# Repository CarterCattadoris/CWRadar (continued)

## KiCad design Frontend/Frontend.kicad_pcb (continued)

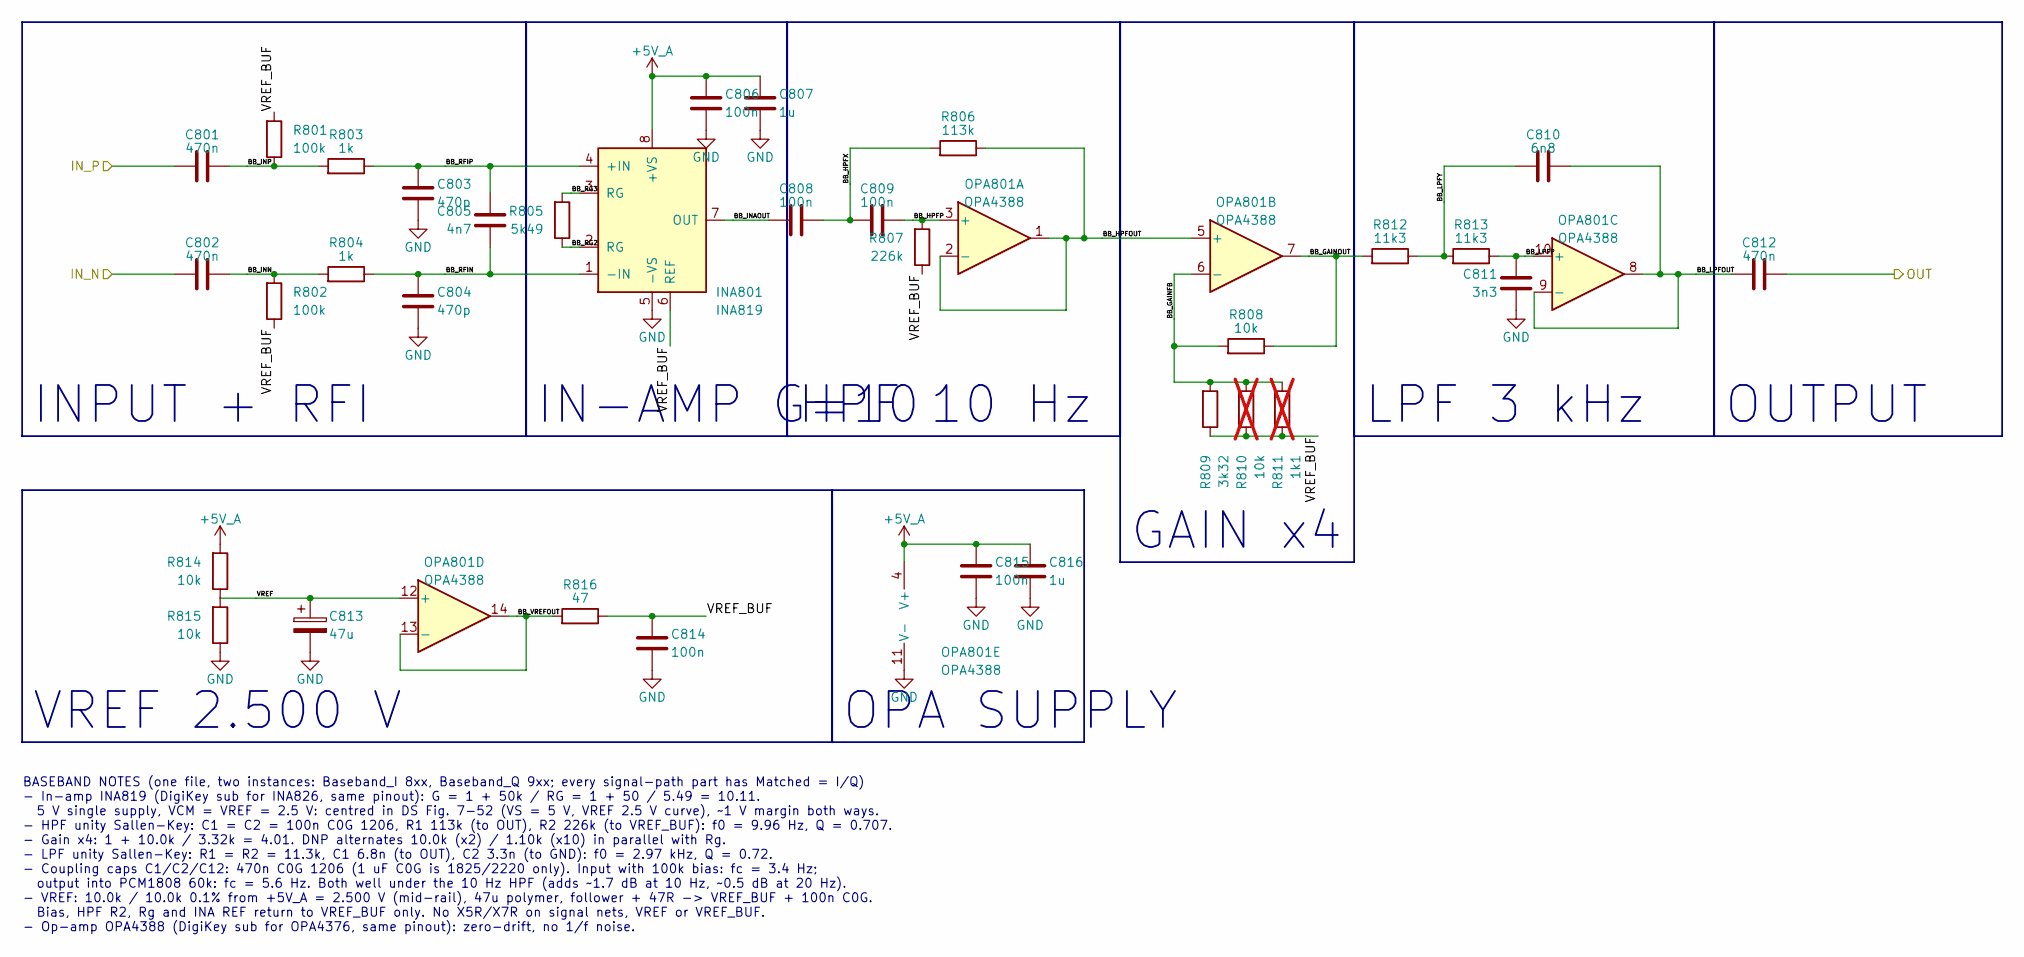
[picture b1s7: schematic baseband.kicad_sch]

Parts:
C801, C802, C812: 470n; C_1206_3216Metric; Mfg Part # GRM31C5C1E474JE01L
C803, C804: 470p; C_0402_1005Metric; Mfg Part # GRM1555C1H471GA01D
C805: 4n7; C_0603_1608Metric; Mfg Part # GCM1885C1H472GA16D
C806, C815: 100n; C_0402_1005Metric; Mfg Part # CL05B104KB54PNC; LCSC C307331
C807, C816: 1u; C_0603_1608Metric; Mfg Part # C0603C105K3RACTU
C808, C809, C814: 100n; C_1206_3216Metric; Mfg Part # GRM3195C2A104GA01D
C810: 6n8; C_0603_1608Metric; Mfg Part # C0603C682F5GACTU
C811: 3n3; C_0603_1608Metric; Mfg Part # GCM1885C1H332FA16D
C813: 47u; CP_EIA-3528-21_Kemet-B; Mfg Part # T520B476M010ATE070
INA801: INA819; SOIC-8_3.9x4.9mm_P1.27mm; Mfg Part # INA819IDR
OPA801: OPA4388; TSSOP-14_4.4x5mm_P0.65mm; Mfg Part # OPA4388IPWR
R801, R802: 100k; R_0402_1005Metric; Mfg Part # RC0402FR-07100KL
R803, R804: 1k; R_0402_1005Metric; Mfg Part # RC0402FR-071KL
R805: 5k49; R_0402_1005Metric; Mfg Part # ERA-2AEB5491X
R806: 113k; R_0402_1005Metric; Mfg Part # RC0402FR-07113KL
R807: 226k; R_0402_1005Metric; Mfg Part # ERJ-2RKF2263X
R808, R814, R815: 10k; R_0402_1005Metric; Mfg Part # ERA-2AEB103X
R809: 3k32; R_0402_1005Metric; Mfg Part # ERA-2AEB3321X
R810: 10k; R_0402_1005Metric; Mfg Part # ERA-2AEB103X; not fitted
R811: 1k1; R_0402_1005Metric; Mfg Part # RG1005P-112-B-T5; not fitted
R812, R813: 11k3; R_0402_1005Metric; Mfg Part # RC0402FR-0711K3L
R816: 47; R_0402_1005Metric; Mfg Part # RC0402FR-0747RL

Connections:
+5V_A: C806.1, C807.1, C815.1, C816.1, INA801.8 (+VS), OPA801.4 (V+), R814.1; also elsewhere on the board
/ADC/ADC_L: C812.2; also elsewhere on the board
/Baseband_I/BB_GAINFB: OPA801.6 (-), R808.1, R809.1, R810.1, R811.1
/Baseband_I/BB_GAINOUT: OPA801.7, R808.2, R812.1
/Baseband_I/BB_HPFOUT: OPA801.1, OPA801.2 (-), OPA801.5 (+), R806.2
/Baseband_I/BB_HPFP: C809.2, OPA801.3 (+), R807.1
/Baseband_I/BB_HPFX: C808.2, C809.1, R806.1
/Baseband_I/BB_INAOUT: C808.1, INA801.7 (OUT)
/Baseband_I/BB_INN: C802.2, R802.1, R804.1
/Baseband_I/BB_INP: C801.2, R801.2, R803.1
/Baseband_I/BB_LPFOUT: C810.2, C812.1, OPA801.8, OPA801.9 (-)
/Baseband_I/BB_LPFP: C811.1, OPA801.10 (+), R813.2
/Baseband_I/BB_LPFY: C810.1, R812.2, R813.1
/Baseband_I/BB_RFIN: C804.1, C805.2, INA801.1 (-IN), R804.2
/Baseband_I/BB_RFIP: C803.1, C805.1, INA801.4 (+IN), R803.2
/Baseband_I/BB_RG2: INA801.2 (RG), R805.2
/Baseband_I/BB_RG3: INA801.3 (RG), R805.1
/Baseband_I/BB_VREFOUT: OPA801.13 (-), OPA801.14, R816.1
/Baseband_I/IN_N: C802.1; also elsewhere on the board
/Baseband_I/IN_P: C801.1; also elsewhere on the board
/Baseband_I/VREF: C813.1, OPA801.12 (+), R814.2, R815.1
/Baseband_I/VREF_BUF: C814.1, INA801.6 (REF), R801.1, R802.2, R807.2, R809.2, R810.2, R811.2, R816.2
GND: C803.2, C804.2, C806.2, C807.2, C811.2, C813.2, C814.2, C815.2, C816.2, INA801.5 (-VS), OPA801.11 (V-), R815.2; also elsewhere on the board

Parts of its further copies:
C901, C902, C912: 470n; C_1206_3216Metric; Mfg Part # GRM31C5C1E474JE01L
C903, C904: 470p; C_0402_1005Metric; Mfg Part # GRM1555C1H471GA01D
C905: 4n7; C_0603_1608Metric; Mfg Part # GCM1885C1H472GA16D
C906, C915: 100n; C_0402_1005Metric; Mfg Part # CL05B104KB54PNC; LCSC C307331
C907, C916: 1u; C_0603_1608Metric; Mfg Part # C0603C105K3RACTU
C908, C909, C914: 100n; C_1206_3216Metric; Mfg Part # GRM3195C2A104GA01D
C910: 6n8; C_0603_1608Metric; Mfg Part # C0603C682F5GACTU
C911: 3n3; C_0603_1608Metric; Mfg Part # GCM1885C1H332FA16D
C913: 47u; CP_EIA-3528-21_Kemet-B; Mfg Part # T520B476M010ATE070
INA901: INA819; SOIC-8_3.9x4.9mm_P1.27mm; Mfg Part # INA819IDR
OPA901: OPA4388; TSSOP-14_4.4x5mm_P0.65mm; Mfg Part # OPA4388IPWR
R901, R902: 100k; R_0402_1005Metric; Mfg Part # RC0402FR-07100KL
R903, R904: 1k; R_0402_1005Metric; Mfg Part # RC0402FR-071KL
R905: 5k49; R_0402_1005Metric; Mfg Part # ERA-2AEB5491X
R906: 113k; R_0402_1005Metric; Mfg Part # RC0402FR-07113KL
R907: 226k; R_0402_1005Metric; Mfg Part # ERJ-2RKF2263X
R908, R914, R915: 10k; R_0402_1005Metric; Mfg Part # ERA-2AEB103X
R909: 3k32; R_0402_1005Metric; Mfg Part # ERA-2AEB3321X
R910: 10k; R_0402_1005Metric; Mfg Part # ERA-2AEB103X; not fitted
R911: 1k1; R_0402_1005Metric; Mfg Part # RG1005P-112-B-T5; not fitted
R912, R913: 11k3; R_0402_1005Metric; Mfg Part # RC0402FR-0711K3L
R916: 47; R_0402_1005Metric; Mfg Part # RC0402FR-0747RL

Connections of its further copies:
+5V_A: C906.1, C907.1, C915.1, C916.1, INA901.8 (+VS), OPA901.4 (V+), R914.1; also elsewhere on the board
/ADC/ADC_R: C912.2; also elsewhere on the board
/Baseband_Q/BB_GAINFB: OPA901.6 (-), R908.1, R909.1, R910.1, R911.1
/Baseband_Q/BB_GAINOUT: OPA901.7, R908.2, R912.1
/Baseband_Q/BB_HPFOUT: OPA901.1, OPA901.2 (-), OPA901.5 (+), R906.2
/Baseband_Q/BB_HPFP: C909.2, OPA901.3 (+), R907.1
/Baseband_Q/BB_HPFX: C908.2, C909.1, R906.1
/Baseband_Q/BB_INAOUT: C908.1, INA901.7 (OUT)
/Baseband_Q/BB_INN: C902.2, R902.1, R904.1
/Baseband_Q/BB_INP: C901.2, R901.2, R903.1
/Baseband_Q/BB_LPFOUT: C910.2, C912.1, OPA901.8, OPA901.9 (-)
/Baseband_Q/BB_LPFP: C911.1, OPA901.10 (+), R913.2
/Baseband_Q/BB_LPFY: C910.1, R912.2, R913.1
/Baseband_Q/BB_RFIN: C904.1, C905.2, INA901.1 (-IN), R904.2
/Baseband_Q/BB_RFIP: C903.1, C905.1, INA901.4 (+IN), R903.2
/Baseband_Q/BB_RG2: INA901.2 (RG), R905.2
/Baseband_Q/BB_RG3: INA901.3 (RG), R905.1
/Baseband_Q/BB_VREFOUT: OPA901.13 (-), OPA901.14, R916.1
/Baseband_Q/IN_N: C902.1; also elsewhere on the board
/Baseband_Q/IN_P: C901.1; also elsewhere on the board
/Baseband_Q/VREF: C913.1, OPA901.12 (+), R914.2, R915.1
/Baseband_Q/VREF_BUF: C914.1, INA901.6 (REF), R901.1, R902.2, R907.2, R909.2, R910.2, R911.2, R916.2
GND: C903.2, C904.2, C906.2, C907.2, C911.2, C913.2, C914.2, C915.2, C916.2, INA901.5 (-VS), OPA901.11 (V-), R915.2; also elsewhere on the board

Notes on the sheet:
INPUT + RFI
IN-AMP G=10
HPF 10 Hz
GAIN x4
LPF 3 kHz
OUTPUT
VREF 2.500 V
OPA SUPPLY
BASEBAND NOTES (one file, two instances: Baseband_I 8xx, Baseband_Q 9xx; every signal-path part has Matched = I/Q) - In-amp INA819 (DigiKey sub for INA826, same pinout): G = 1 + 50k / RG = 1 + 50 / 5.49 = 10.11. 5 V single supply, VCM = VREF = 2.5 V: centred in DS Fig. 7-52 (VS = 5 V, VREF 2.5 V cu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

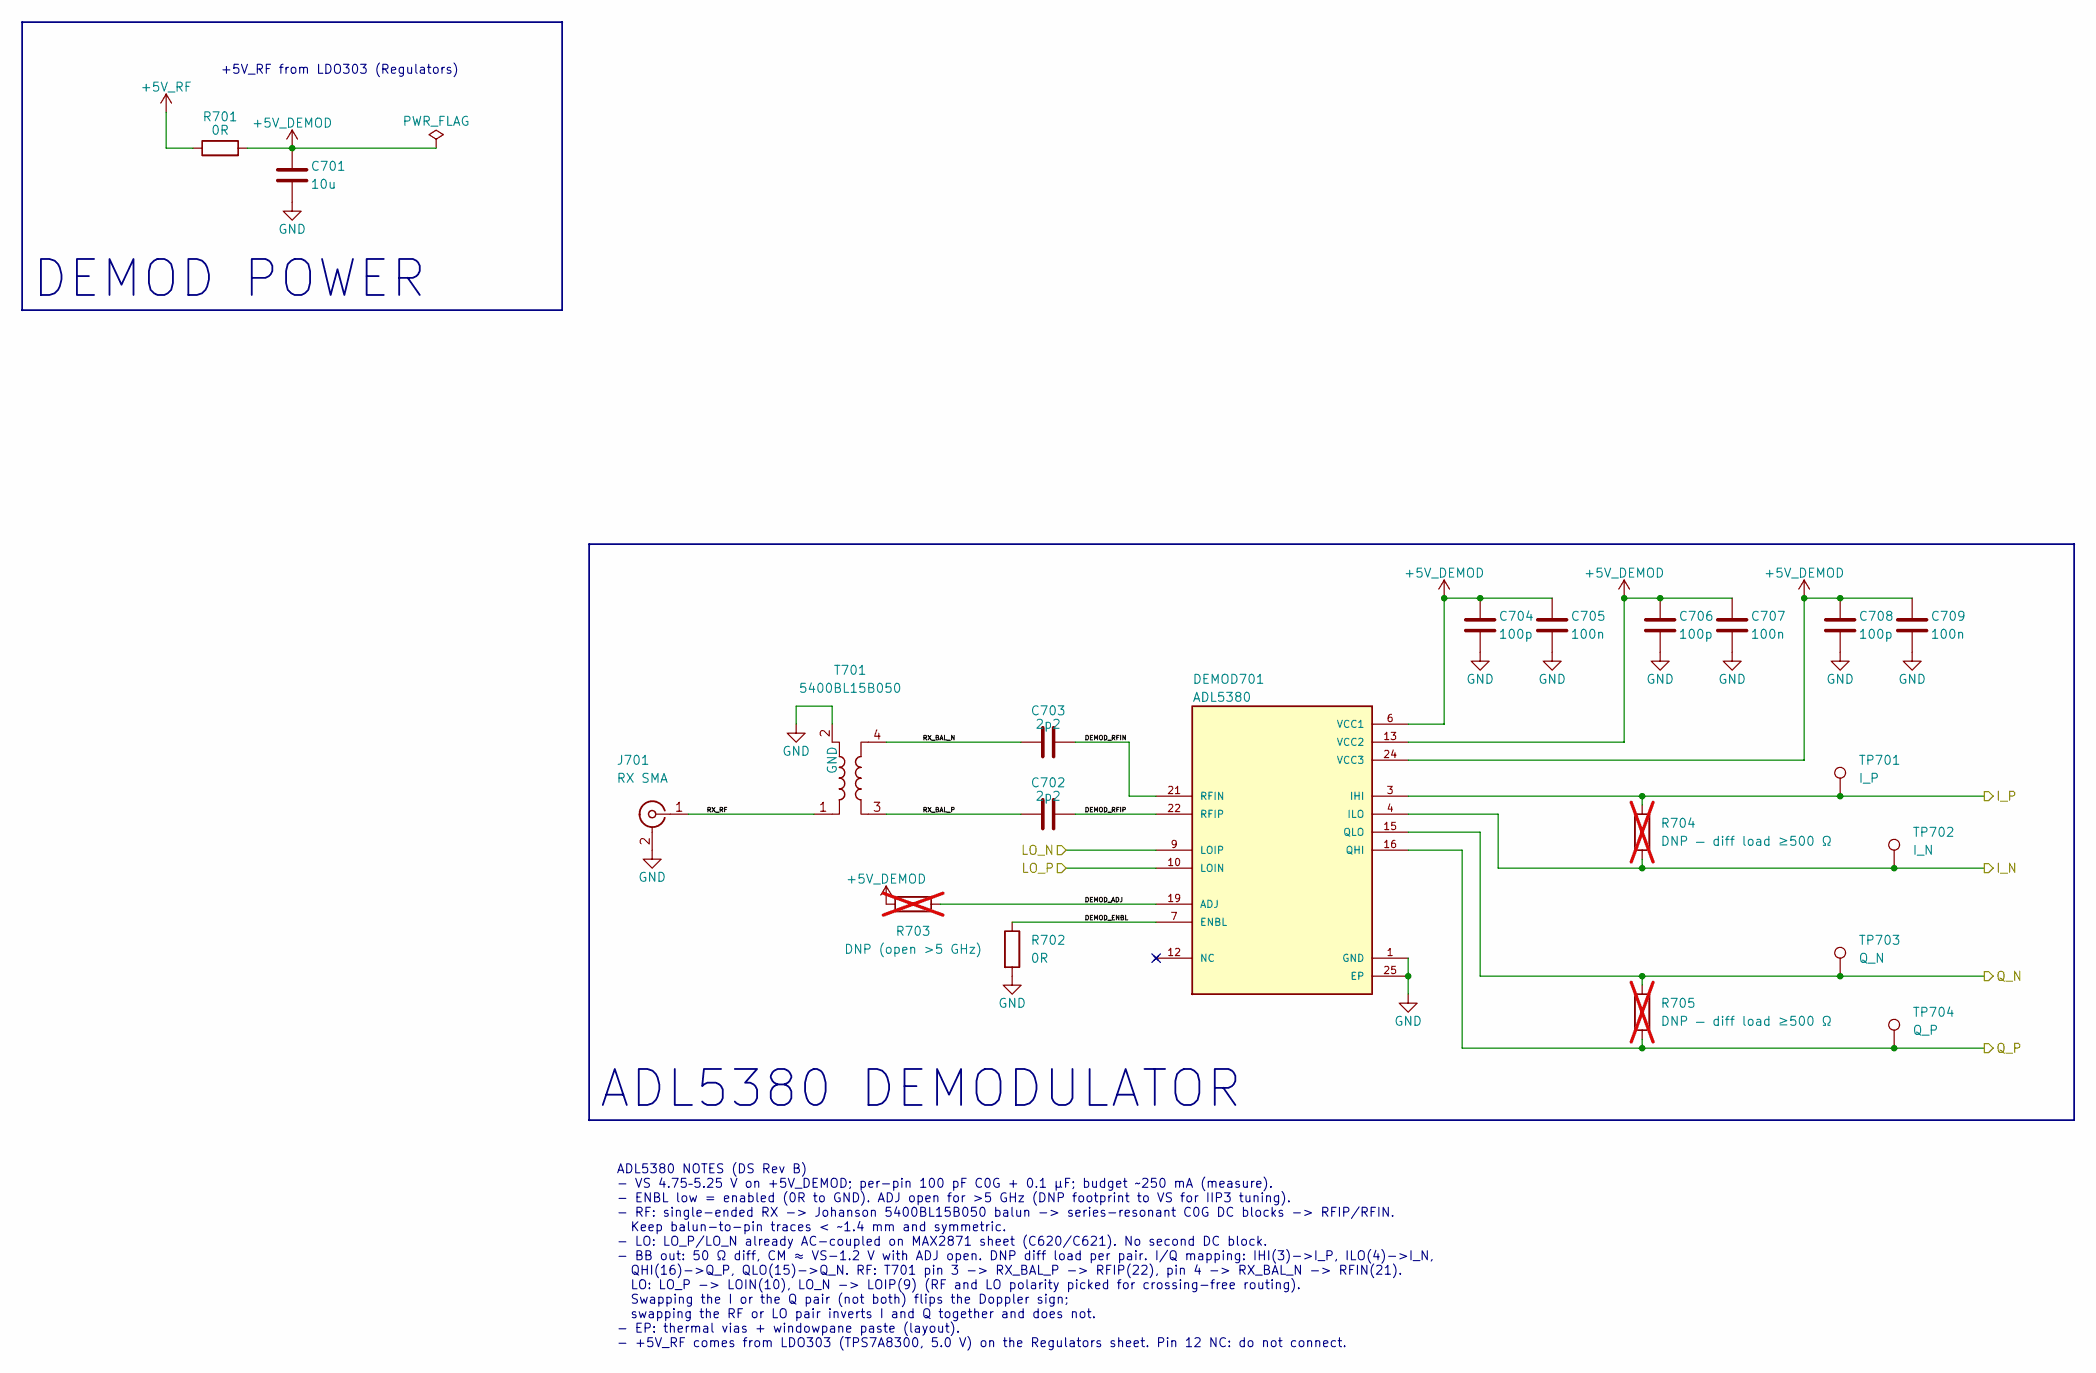
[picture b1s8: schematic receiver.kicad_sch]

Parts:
C701: 10u; C_0805_2012Metric; Mfg Part # CL21B106KOQNNNE; LCSC C95841
C702, C703: 2p2; C_0402_1005Metric; Mfg Part # GJM1555C1H2R2BB01D
C704, C706, C708: 100p; C_0402_1005Metric; Mfg Part # GRM1555C1H101JA01D
C705, C707, C709: 100n; C_0402_1005Metric; Mfg Part # CL05B104KB54PNC; LCSC C307331
DEMOD701: ADL5380; 24-WFQFN; Mfg Part # ADL5380ACPZ-R7
J701: RX SMA; SMA_Molex_73251-1153_EdgeMount_Horizontal; Mfg Part # 0732511153
R701: 0R; R_0603_1608Metric; Mfg Part # RC0603JR-070RL; LCSC C95177
R702: 0R; R_0402_1005Metric; Mfg Part # RC0402JR-070RL
R703: DNP (open >5 GHz); R_0402_1005Metric; not fitted
R704, R705: DNP — diff load ≥500 Ω; R_0402_1005Metric; not fitted
T701: 5400BL15B050; Balun_Johanson_5400BL15B050E; Mfg Part # 5400BL15B0050001E
TP701: I_P; TestPoint_Pad_D1.0mm
TP702: I_N; TestPoint_Pad_D1.0mm
TP703: Q_N; TestPoint_Pad_D1.0mm
TP704: Q_P; TestPoint_Pad_D1.0mm

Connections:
+5V_DEMOD: C701.1, C704.1, C705.1, C706.1, C707.1, C708.1, C709.1, DEMOD701.6 (VCC1), DEMOD701.13 (VCC2), DEMOD701.24 (VCC3), R701.2, R703.1
+5V_RF: R701.1; also elsewhere on the board
/Baseband_I/IN_N: DEMOD701.4 (ILO), R704.2, TP702.1 (1_1); also elsewhere on the board
/Baseband_I/IN_P: DEMOD701.3 (IHI), R704.1, TP701.1 (1_1); also elsewhere on the board
/Baseband_Q/IN_N: DEMOD701.15 (QLO), R705.1, TP703.1 (1_1); also elsewhere on the board
/Baseband_Q/IN_P: DEMOD701.16 (QHI), R705.2, TP704.1 (1_1); also elsewhere on the board
/Receiver/DEMOD_ADJ: DEMOD701.19 (ADJ), R703.2
/Receiver/DEMOD_ENBL: DEMOD701.7 (ENBL), R702.1
/Receiver/DEMOD_RFIN: C703.2, DEMOD701.21 (RFIN)
/Receiver/DEMOD_RFIP: C702.2, DEMOD701.22 (RFIP)
/Receiver/LO_N: DEMOD701.9 (LOIP); also elsewhere on the board
/Receiver/LO_P: DEMOD701.10 (LOIN); also elsewhere on the board
/Receiver/RX_BAL_N: C703.1, T701.4
/Receiver/RX_BAL_P: C702.1, T701.3
/Receiver/RX_RF: J701.1 (In), T701.1
GND: C701.2, C704.2, C705.2, C706.2, C707.2, C708.2, C709.2, DEMOD701.1 (GND), DEMOD701.2 (GND), DEMOD701.5 (GND), DEMOD701.8 (GND), DEMOD701.11 (GND), DEMOD701.14 (GND), DEMOD701.17 (GND), DEMOD701.18 (GND), DEMOD701.20 (GND), DEMOD701.23 (GND), DEMOD701.25 (EP), DEMOD701.25_1 (EP), DEMOD701.25_2 (EP), DEMOD701.25_3 (EP), DEMOD701.25_4 (EP), DEMOD701.25_5 (EP), DEMOD701.25_6 (EP), DEMOD701.25_7 (EP), DEMOD701.25_8 (EP), DEMOD701.25_9 (EP), J701.2 (Ext), R702.2, T701.2 (GND), T701.5 (GND); also elsewhere on the board

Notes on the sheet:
+5V_RF from LDO303 (Regulators)
ADL5380 NOTES (DS Rev B) - VS 4.75–5.25 V on +5V_DEMOD; per-pin 100 pF C0G + 0.1 µF; budget ~250 mA (measure). - ENBL low = enabled (0R to GND). ADJ open for >5 GHz (DNP footprint to VS for IIP3 tuning). - RF: single-ended RX -> Johanson 5400BL15B050 balun -> series-resonant C0G DC blocks -> RFIP/R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
ADL5380 DEMODULATOR
DEMOD POWER

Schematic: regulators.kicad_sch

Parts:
BUCK301, BUCK302: TPS62933F; SOT-583-8; Mfg Part # TPS62933FDRLR
C301, C307: 10u; C_0805_2012Metric; Mfg Part # TMK212BBJ106KD-T
C302, C304, C308, C310, C314, C319, C324, C329: 100n; C_0402_1005Metric; Mfg Part # CL05B104KB54PNC; LCSC C307331
C303, C309: 22n; C_0402_1005Metric; Mfg Part # CL05B223KB5NNNC
C305, C306, C311, C312: 22u; C_1206_3216Metric; Mfg Part # 12063D226KAT2A
C313, C318, C323, C328, C333: 10u; C_0805_2012Metric; Mfg Part # CL21B106KOQNNNE; LCSC C95841
C315, C316, C320, C321, C325, C326, C330, C331: 10n; C_0402_1005Metric; Mfg Part # CL05B103KB5NNNC
C317, C322, C327, C332: 47u; C_1206_3216Metric; Mfg Part # GRM31CR61A476ME15L
C334: 1u; C_0603_1608Metric; Mfg Part # C0603C105K3RACTU
J301: PH_2P; JST_PH_B2B-PH-K_1x02_P2.00mm_Vertical; Mfg Part # B2B-PH-K-S
L301: 10uH; L_Bourns_SRP7028A_7.3x6.6mm; Mfg Part # SRP7028A-100M
L302: 6.8uH; L_Wuerth_MAPI-4020; Mfg Part # 74438357068
LDO303, LDO304, LDO305, LDO306: TPS7A8300; QFN-20-1EP_3.5x3.5mm_P0.5mm_EP2x2mm_ThermalVias; Mfg Part # TPS7A8300RGRR
R301: 0R; R_0603_1608Metric; Mfg Part # RC0603JR-070RL; LCSC C95177
R302: 51k1; R_0402_1005Metric; Mfg Part # RC0402FR-0751K1L
R303: 60k4; R_0402_1005Metric; Mfg Part # RC0402FR-0760K4L
R304, R307: 10k; R_0402_1005Metric; Mfg Part # RC0402FR-0710KL
R305: 20k5; R_0402_1005Metric; Mfg Part # RC0402FR-0720K5L
R306: 31k6; R_0402_1005Metric; Mfg Part # RC0402FR-0731K6L
R308: 113k; R_0402_1005Metric; Mfg Part # RC0402FR-07113KL
R309: 30k9; R_0402_1005Metric; Mfg Part # RC0402FR-0730K9L
R310, R312, R314: 105k; R_0402_1005Metric; Mfg Part # RT0402BRD07105KL
R311, R313, R315: 20k; R_0402_1005Metric; Mfg Part # ERA-2AEB203X
SW301: SW_SLIDE; SW_Slide_SPDT_Straight_CK_OS102011MS2Q; Mfg Part # OS102011MS2QN1
TP301: EN_BUCK; TestPoint_Pad_D1.0mm
TP302: +5V_RF; TestPoint_Pad_D1.0mm
TP303, TP305, TP307, TP309: PG; TestPoint_Pad_D1.0mm
TP304: +5V_A; TestPoint_Pad_D1.0mm
TP306: +3V3_SYN; TestPoint_Pad_D1.0mm
TP308: +V_LNA; TestPoint_Pad_D1.0mm
TP310: +VPRE; TestPoint_Pad_D1.0mm
TP311: +3V3_D; TestPoint_Pad_D1.0mm

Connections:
+3V3_D: C311.1, C312.1, L302.2, R306.1, TP311.1 (1_1); also elsewhere on the board
+3V3_SYN: C326.1, C327.1, LDO305.1 (OUT), LDO305.2 (SNS), LDO305.19 (OUT), LDO305.20 (OUT), TP306.1 (1_1); also elsewhere on the board
+5V_A: C321.1, C322.1, LDO304.1 (OUT), LDO304.19 (OUT), LDO304.20 (OUT), R312.1, TP304.1 (1_1); also elsewhere on the board
+5V_RF: C316.1, C317.1, LDO303.1 (OUT), LDO303.19 (OUT), LDO303.20 (OUT), R310.1, TP302.1 (1_1); also elsewhere on the board
+VPRE: C305.1, C306.1, C313.1, C314.1, C318.1, C319.1, C323.1, C324.1, C328.1, C329.1, L301.2, LDO303.14 (EN), LDO303.15 (IN), LDO303.16 (IN), LDO303.17 (IN), LDO304.14 (EN), LDO304.15 (IN), LDO304.16 (IN), LDO304.17 (IN), LDO305.14 (EN), LDO305.15 (IN), LDO305.16 (IN), LDO305.17 (IN), LDO306.15 (IN), LDO306.16 (IN), LDO306.17 (IN), R303.1, TP310.1 (1_1)
+VSYS: BUCK301.3 (VIN), BUCK302.3 (VIN), C301.1, C302.1, C307.1, C308.1, R308.1; also elsewhere on the board
+V_LNA: C331.1, C332.1, LDO306.1 (OUT), LDO306.19 (OUT), LDO306.20 (OUT), R301.1, R314.1, TP308.1 (1_1)
/MCU/EN_ANALOG: LDO306.14 (EN); also elsewhere on the board
/Regulators/BUCK1_BST: BUCK301.6 (BST), C304.1
/Regulators/BUCK1_FB: BUCK301.8 (FB), R303.2, R304.1
/Regulators/BUCK1_RT: BUCK301.1 (RT), R302.1
/Regulators/BUCK1_SS: BUCK301.7 (SS), C303.1
/Regulators/BUCK1_SW: BUCK301.5 (SW), C304.2, L301.1
/Regulators/BUCK2_BST: BUCK302.6 (BST), C310.1
/Regulators/BUCK2_FB: BUCK302.8 (FB), R306.2, R307.1
/Regulators/BUCK2_RT: BUCK302.1 (RT), R305.1
/Regulators/BUCK2_SS: BUCK302.7 (SS), C309.1
/Regulators/BUCK2_SW: BUCK302.5 (SW), C310.2, L302.1
/Regulators/EN_BUCK: BUCK301.2 (EN), BUCK302.2 (EN), R308.2, R309.1, SW301.2 (B), TP301.1 (1_1)
/Regulators/LDO3_FB: C316.2, LDO303.3 (FB), R310.2, R311.1
/Regulators/LDO3_NR: C315.1, LDO303.13 (NR/SS)
/Regulators/LDO3_PG: LDO303.4 (PG), TP303.1 (1_1)
/Regulators/LDO4_FB: C321.2, LDO304.3 (FB), R312.2, R313.1
/Regulators/LDO4_NR: C320.1, LDO304.13 (NR/SS)
/Regulators/LDO4_PG: LDO304.4 (PG), TP305.1 (1_1)
/Regulators/LDO5_FB: C326.2, LDO305.3 (FB)
/Regulators/LDO5_NR: C325.1, LDO305.13 (NR/SS)
/Regulators/LDO5_PG: LDO305.4 (PG), TP307.1 (1_1)
/Regulators/LDO6_FB: C331.2, LDO306.3 (FB), R314.2, R315.1
/Regulators/LDO6_NR: C330.1, LDO306.13 (NR/SS)
/Regulators/LDO6_PG: LDO306.4 (PG), TP309.1 (1_1)
/Regulators/LNA_5V: C333.1, C334.1, J301.1, R301.2
GND: BUCK301.4 (GND), BUCK302.4 (GND), C301.2, C302.2, C303.2, C305.2, C306.2, C307.2, C308.2, C309.2, C311.2, C312.2, C313.2, C314.2, C315.2, C317.2, C318.2, C319.2, C320.2, C322.2, C323.2, C324.2, C325.2, C327.2, C328.2, C329.2, C330.2, C332.2, C333.2, C334.2, J301.2, LDO303.8 (GND), LDO303.18 (GND), LDO303.21 (EP), LDO304.8 (GND), LDO304.18 (GND), LDO304.21 (EP), LDO305.6 (100mV), LDO305.8 (GND), LDO305.10 (800mV), LDO305.11 (1.6V), LDO305.18 (GND), LDO305.21 (EP), LDO306.8 (GND), LDO306.18 (GND), LDO306.21 (EP), R302.2, R304.2, R305.2, R307.2, R309.2, R311.2, R313.2, R315.2, SW301.1 (A); also elsewhere on the board

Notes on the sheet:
ON (open)
+V_LNA LDO (ANTENNA BOARD)
SW301 only switches EN_BUCK (no load current); charging continues when OFF. EN divider, both EN pins in parallel (Ip, Ih doubled), DS Eq. 3-5: R1 = 113k, R2 = 30.9k -> start 5.48 V, stop 4.97 V; VEN at 8.8 V = 2.0 V (< 5.5 V, abs max 6 V).
3V3 DIGITAL BUCK
OFF
TEST POINTS
+5V_A LDO (BASEBAND + ADC)
+5V_RF LDO (ADL5380)
REGULATOR NOTES (TPS62933F SLUSEA4D, TPS7A8300 SBVS197F) - FB: VOUT = 0.8 V x (1 + Rtop/Rbot). BUCK301 60.4k/10.0k = 5.63 V; BUCK302 31.6k/10.0k = 3.33 V (TI start 10.2k). - fSW: RT from Eq. 2, fSW = 17293 x RT^-0.942. BUCK302 RT 20.5k = 1.0 MHz. BUCK301: Eq. 10 VIN_MIN = VOUT / (1 - fSW x tOFF_MIN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
LNA POWER
J301 pin 1 = +V_LNA, pin 2 = GND. Silk: "LNA 5V". Place beside the RX connector.
5V6 PRE-BUCK
+3V3_SYN LDO (MAX2871)
BUCK ENABLE

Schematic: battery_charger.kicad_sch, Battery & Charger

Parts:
C201: 1u; C_0603_1608Metric; Mfg Part # C0603C105K3RACTU
C202: 10u; C_0805_2012Metric; Mfg Part # TMK212BBJ106KD-T
C203: 47n; C_0402_1005Metric; Mfg Part # GRM155R71H473KE14D
C204, C205, C206, C207, C208, C209: 22u; C_1206_3216Metric; Mfg Part # 12063D226KAT2A
C210: 4u7; C_0603_1608Metric; Mfg Part # GRM188R61E475KE11D
CHG201: BQ25883; Texas_RGE0024H_VQFN-24-1EP_4x4mm_P0.5mm_EP2.7x2.7mm_Thermal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; Mfg Part # BQ25883RGET
D201: ORG; LED_0603_1608Metric; Mfg Part # LTST-C191KFKT
D204: SMF6.5A; D_SOD-123F; Mfg Part # SMF6.5A-TP
ESD202, ESD203: USBLC6-2SC6; SOT-23-6; Mfg Part # USBLC6-2SC6
F201: 3A; Fuse_1206_3216Metric; Mfg Part # 0466003.NR
J201: XH_2P; JST_XH_B2B-XH-A_1x02_P2.50mm_Vertical; Mfg Part # B2B-XH-A
J203: PH_2P; JST_PH_B2B-PH-K_1x02_P2.00mm_Vertical; Mfg Part # B2B-PH-K-S; not fitted
L201: 1uH; L_Wuerth_MAPI-4020; Mfg Part # 74438357010
Q201: AO3401A; SOT-23; Mfg Part # AO3401A
R201: 0R; R_0603_1608Metric; Mfg Part # RC0603JR-070RL; LCSC C95177
R202, R203: 0R; R_0402_1005Metric; Mfg Part # RC0402JR-070RL
R204, R206: 5k1; R_0402_1005Metric; Mfg Part # RC0402FR-075K1L
R205, R207, R208: 10k; R_0402_1005Metric; Mfg Part # RC0402FR-0710KL
R209: 392; R_0402_1005Metric; Mfg Part # RC0402FR-07392RL
R210: 5k23; R_0402_1005Metric; Mfg Part # RC0402FR-075K23L
R211: 30k1; R_0402_1005Metric; Mfg Part # RC0402FR-0730K1L
R212: 100k; R_0402_1005Metric; Mfg Part # RC0402FR-07100KL
R213: 1k5; R_0402_1005Metric; Mfg Part # ERJ-2RKF1501X
RT201: 10k B3435; R_0603_1608Metric; Mfg Part # NTCG163JF103FT1S
TP201: CHG_INT; TestPoint_Pad_D1.0mm
TP202: CHG_PG; TestPoint_Pad_D1.0mm
TP203: +VBUS; TestPoint_Pad_D1.0mm
TP204: +VBAT; TestPoint_Pad_D1.0mm
TP205: +VSYS; TestPoint_Pad_D1.0mm
TP206: GND; TestPoint_Pad_D1.0mm
USB201: USB4105-GF-A; USB_C_Receptacle_GCT_USB4105-xx-A_16P_TopMnt_Horizontal; Mfg Part # USB4105-GF-A

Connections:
+3V3_D: R208.1; also elsewhere on the board
+VBAT: C208.1, C209.1, CHG201.13 (BAT), CHG201.14 (BAT), Q201.2 (S), TP204.1 (1_1)
+VBUS: C201.1, CHG201.23 (VBUS), D204.1 (K), ESD202.5 (VBUS), ESD203.5 (VBUS), TP203.1 (1_1), USB201.A4 (VBUS), USB201.A9 (VBUS), USB201.B4 (VBUS), USB201.B9 (VBUS)
+VSYS: C204.1, C205.1, C206.1, C207.1, CHG201.15 (SYS), CHG201.16 (SYS), TP205.1 (1_1); also elsewhere on the board
/Battery_Charger/BATT_FUSED: F201.2, Q201.3 (D)
/Battery_Charger/BATT_GATE: Q201.1 (G), R212.1
/Battery_Charger/BATT_IN: F201.1, J201.1
/Battery_Charger/CC1_SENSE: R205.2; also elsewhere on the board
/Battery_Charger/CC2_SENSE: R207.2; also elsewhere on the board
/Battery_Charger/CHG_BTST: C203.2, CHG201.12 (BTST)
/Battery_Charger/CHG_DN: CHG201.1 (D-), R202.1
/Battery_Charger/CHG_DP: CHG201.24 (D+), R203.2
/Battery_Charger/CHG_ILIM: CHG201.8 (ILIM), R209.2
/Battery_Charger/CHG_INT: CHG201.6 (~INT), R208.2, TP201.1 (1_1); also elsewhere on the board
/Battery_Charger/CHG_LED_A: D201.2 (A), R213.2
/Battery_Charger/CHG_PG: CHG201.9 (~PG), TP202.1 (1_1)
/Battery_Charger/CHG_PMID: C202.1, CHG201.21 (PMID), CHG201.22 (PMID), L201.1
/Battery_Charger/CHG_REGN: C210.1, CHG201.11 (REGN), R210.1, R213.1
/Battery_Charger/CHG_STAT: CHG201.2 (STAT), D201.1 (K)
/Battery_Charger/CHG_SW: C203.1, CHG201.17 (SW), CHG201.18 (SW), L201.2
/Battery_Charger/CHG_TS: CHG201.7 (TS), J203.1, R210.2, R211.1, RT201.1
/Battery_Charger/USBC_CC1: ESD203.1 (I/O1), USB201.A5 (CC1)
/Battery_Charger/USBC_CC2: ESD203.3 (I/O2), USB201.B5 (CC2)
/Battery_Charger/USBC_DN: ESD202.1 (I/O1), USB201.A7 (D-), USB201.B7 (D-)
/Battery_Charger/USBC_DP: ESD202.3 (I/O2), USB201.A6 (D+), USB201.B6 (D+)
/Battery_Charger/USB_CC1: ESD203.6 (I/O1), R204.1, R205.1
/Battery_Charger/USB_CC2: ESD203.4 (I/O2), R206.1, R207.1
/Battery_Charger/USB_D_N: ESD202.6 (I/O1), R202.2; also elsewhere on the board
/Battery_Charger/USB_D_P: ESD202.4 (I/O2), R203.1; also elsewhere on the board
/Battery_Charger/USB_SHIELD: R201.1, USB201.SH (SHIELD)
/I2C_SCL: CHG201.5 (SCL); also elsewhere on the board
/I2C_SDA: CHG201.4 (SDA); also elsewhere on the board
GND: C201.2, C202.2, C204.2, C205.2, C206.2, C207.2, C208.2, C209.2, C210.2, CHG201.3 (~CE), CHG201.19 (GND), CHG201.20 (GND), CHG201.25 (EP), D204.2 (A), ESD202.2 (GND), ESD203.2 (GND), J201.2, J203.2, R201.2, R204.2, R206.2, R209.1, R211.2, R212.2, RT201.2, TP206.1 (1_1), USB201.A1 (GND), USB201.A12 (GND), USB201.B1 (GND), USB201.B12 (GND); also elsewhere on the board

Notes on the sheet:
CHARGER NOTES (BQ25883 SLUSDL3A) - ILIM: IINMAX = KILIM / RILIM (Eq. 3). KILIM 1012 / 1098 / 1185 (min/typ/max). RILIM = 392R -> 2.58 / 2.80 / 3.02 A: worst case stays at the 3.0 A USB-C cap. Firmware sets IINDPM per CC1/CC2_SENSE. - TS: DS 8.3.7.4.1 Eq. 1-2 for 103AT, 0-60 C: RT1 = 5.24k -> 5.23k 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
CHARGER
Amber, lights only with USB present (REGN on). (5.0 - 1.9) V / 1k5 = ~2 mA. STAT sinks <= 6 mA, abs max 6 V.
RT201 and J203 are alternatives — populate one. J203: external 10k NTC taped to the pack.
USB-C INPUT
BATTERY INPUT
CHARGE LED
TEST POINTS
Generic pack leads vary in polarity — verify pin 1 = + before connecting. Pack has a built-in BMS: no on-board cell protection, no VBAT divider (BQ25883 ADC reads VBAT/VSYS). Q201: drain to F201, source to +VBAT; body-diode anode toward J201. Correct polarity: VGS = -VBAT (-6 to -8.4 V, inside ±12 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

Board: 4 copper layers, 311 parts (4 on the bottom side), 181 nets, no tracks yet.

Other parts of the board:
FID1101, FID1102, FID1103: Fiducial; Fiducial_1mm_Mask2mm

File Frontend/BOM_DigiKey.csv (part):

Quantity,Manufacturer Part Number,Manufacturer,Customer Reference,Description,DigiKey URL
1,PCM1808PWR,Texas Instruments,ADC1001,PCM1808,https://www.digikey.com/en/products/detail/texas-instruments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
2,TPS62933FDRLR,Texas Instruments,"BUCK301,BUCK302",TPS62933F,https://www.digikey.com/en/products/detail/texas-instruments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
6,C0603C105K3RACTU,KEMET,"C201,C334,C807,C816,C907,C916",1u,https://www.digikey.com/en/products/detail/kemet/C0603C105K3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
3,TMK212BBJ106KD-T,Taiyo Yuden,"C202,C301,C307",10u,https://www.digikey.com/en/products/detail/taiyo-yuden/TMK21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
1,GRM155R71H473KE14D,Murata,C203,47n,https://www.digikey.com/en/products/detail/murata-electronic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
11,12063D226KAT2A,KYOCERA AVX,"C204,C205,C206,C207,C208,C209,C305,C306,C311,C312,C401",22u,https://www.digikey.com/en/products/detail/kyocera-avx/12063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
1,GRM188R61E475KE11D,Murata,C210,4u7,https://www.digikey.com/en/products/detail/murata-electronic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
23,CL05B104KB54PNC,Samsung Electro Mechanics,"C302,C304,C308,C310,C314,C319,C324,C329,C402,C502,C503,C504,C605,C705,C707,C709,C806,C815,C906,C915,C1002,C1004,C1006",100n,https://www.digikey.com/en/products/detail/samsung-electro-m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
2,CL05B223KB5NNNC,Samsung,"C303,C309",22n,https://www.digikey.com/en/products/detail/samsung-electro-m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
12,CL21B106KOQNNNE,Samsung,"C313,C318,C323,C328,C333,C501,C601,C604,C701,C1001,C1003,C1005",10u,https://www.digikey.com/en/products/detail/samsung-electro-m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
9,CL05B103KB5NNNC,Samsung,"C315,C316,C320,C321,C325,C326,C330,C331,C606",10n,https://www.digikey.com/en/products/detail/samsung-electro-m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
4,GRM31CR61A476ME15L,Murata,"C317,C322,C327,C332",47u,https://www.digikey.com/en/products/detail/murata-electronic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
14,CL05A105KP5NNNC,Samsung,"C403,C602,C603,C607,C608,C609,C611,C612,C613,C614,C615,C616,C625,C628",1u,https://www.digikey.com/en/products/detail/samsung-electro-m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
9,GJM1555C1H2R2BB01D,Murata,"C610,C618,C619,C620,C621,C626,C627,C702,C703",2p2,https://www.digikey.com/en/products/detail/murata-electronic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
1,GRM1555C1H102JA01D,Murata,C617,1n,https://www.digikey.com/en/products/detail/murata-electronic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
1,C0603C123J3GACTU,KEMET,C622,12n,https://www.digikey.com/en/products/detail/kemet/C0603C123J3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
1,GRM1555C1H821JA01D,Murata,C624,820p,https://www.digikey.com/en/products/detail/murata-electronic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
3,GRM1555C1H101JA01D,Murata,"C704,C706,C708",100p,https://www.digikey.com/en/products/detail/murata-electronic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
6,GRM31C5C1E474JE01L,Murata,"C801,C802,C812,C901,C902,C912",470n,https://www.digikey.com/en/products/detail/murata-electronic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
4,GRM1555C1H471GA01D,Murata,"C803,C804,C903,C904",470p,https://www.digikey.com/en/products/detail/murata-electronic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
2,GCM1885C1H472GA16D,Murata,"C805,C905",4n7,https://www.digikey.com/en/products/detail/murata-electronic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
7,GRM3195C2A104GA01D,Murata,"C623,C808,C809,C814,C908,C909,C914",100n,https://www.digikey.com/en/products/detail/murata-electronic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
2,C0603C682F5GACTU,KEMET,"C810,C910",6n8,https://www.digikey.com/en/products/detail/kemet/C0603C682F5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
2,GCM1885C1H332FA16D,Murata,"C811,C911",3n3,https://www.digikey.com/en/products/detail/murata-electronic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
2,T520B476M010ATE070,KEMET,"C813,C913",47u,https://www.digikey.com/en/products/detail/kemet/T520B476M01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
1,BQ25883RGET,Texas Instruments,CHG201,BQ25883,https://www.digikey.com/en/products/detail/texas-instruments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
1,LTST-C191KFKT,Lite-On,D201,ORG,https://www.digikey.com/en/products/detail/liteon/LTST-C191K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
1,SMF6.5A-TP,MCC,D204,SMF6.5A,https://www.digikey.com/en/products/detail/mcc-micro-commerc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
1,LTST-C191KGKT,Lite-On,D501,GRN,https://www.digikey.com/en/products/detail/liteon/LTST-C191K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
1,LTST-C191KSKT,Lite-On,D502,YEL,https://www.digikey.com/en/products/detail/liteon/LTST-C191K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
1,LTST-C191KRKT,Lite-On,D503,RED,https://www.digikey.com/en/products/detail/liteon/LTST-C191K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
1,ADL5380ACPZ-R7,Analog Devices,DEMOD701,ADL5380,https://www.digikey.com/en/products/detail/analog-devices-in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
2,USBLC6-2SC6,STMicroelectronics,"ESD202,ESD203",USBLC6-2SC6,https://www.digikey.com/en/products/detail/stmicroelectronic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
1,0466003.NR,Littelfuse,F201,3A,https://www.digikey.com/en/products/detail/littelfuse-inc/04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
2,INA819IDR,Texas Instruments,"INA801,INA901",INA819,https://www.digikey.com/en/products/detail/texas-instruments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
1,B2B-XH-A,JST,J201,XH_2P,https://www.digikey.com/en/products/detail/jst-sales-america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
1,B2B-PH-K-S,JST,J301,PH_2P,https://www.digikey.com/en/products/detail/jst-sales-america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
1,61201021621,Würth Elektronik,J501,BOX_2x05,https://www.digikey.com/en/products/detail/w%C3%BCrth-elektr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
1,0732511153,Molex,J601,TX SMA,https://www.digikey.com/en/products/detail/molex/0732511153/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
1,0732511153,Molex,J701,RX SMA,https://www.digikey.com/en/products/detail/molex/0732511153/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
1,74438357010,Würth Elektronik,L201,1uH,https://www.digikey.com/en/products/detail/w%C3%BCrth-elektr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
1,SRP7028A-100M,Bourns,L301,10uH,https://www.digikey.com/en/products/detail/bourns-inc/SRP702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
1,74438357068,Würth Elektronik,L302,6.8uH,https://www.digikey.com/en/products/detail/w%C3%BCrth-elektr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
4,TPS7A8300RGRR,Texas Instruments,"LDO303,LDO304,LDO305,LDO306",TPS7A8300,https://www.digikey.com/en/products/detail/texas-instruments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
1,ESP32-S3-WROOM-1-N16R2,Espressif,MCU401,ESP32-S3-WROOM-1-N16R2,https://www.digikey.com/en/products/detail/espressif-systems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
2,OPA4388IPWR,Texas Instruments,"OPA801,OPA901",OPA4388,https://www.digikey.com/en/products/detail/texas-instruments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
1,MAX2871ETJ+T,Analog Devices,PLL601,MAX2871ETJ_T,https://www.digikey.com/en/products/detail/analog-devices-in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
1,AO3401A,Alpha & Omega,Q201,AO3401A,https://www.digikey.com/en/products/detail/alpha-omega-semic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
1,2N7002K,onsemi,Q501,2N7002K,https://www.digikey.com/en/products/detail/onsemi/2N7002K/2060348
7,RC0603JR-070RL,YAGEO,"R201,R301,R601,R602,R603,R618,R701",0R,https://www.digikey.com/en/products/detail/yageo/RC0603JR-07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
5,RC0402JR-070RL,YAGEO,"R202,R203,R403,R404,R702",0R,https://www.digikey.com/en/products/detail/yageo/RC0402JR-07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
3,RC0402FR-075K1L,YAGEO,"R204,R206,R610",5k1,https://www.digikey.com/en/products/detail/yageo/RC0402FR-07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
10,RC0402FR-0710KL,YAGEO,"R205,R207,R208,R304,R307,R401,R402,R507,R508,R1001",10k,https://www.digikey.com/en/products/detail/yageo/RC0402FR-07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
1,RC0402FR-07392RL,YAGEO,R209,392,https://www.digikey.com/en/products/detail/yageo/RC0402FR-07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
1,RC0402FR-075K23L,YAGEO,R210,5k23,https://www.digikey.com/en/products/detail/yageo/RC0402FR-07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
1,RC0402FR-0730K1L,YAGEO,R211,30k1,https://www.digikey.com/en/products/detail/yageo/RC0402FR-07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
9,RC0402FR-07100KL,YAGEO,"R212,R410,R608,R609,R619,R801,R802,R901,R902",100k,https://www.digikey.com/en/products/detail/yageo/RC0402FR-07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
2,ERJ-2RKF1501X,Panasonic,"R213,R509",1k5,https://www.digikey.com/en/products/detail/panasonic-industr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
1,RC0402FR-0751K1L,YAGEO,R302,51k1,https://www.digikey.com/en/products/detail/yageo/RC0402FR-07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
1,RC0402FR-0760K4L,YAGEO,R303,60k4,https://www.digikey.com/en/products/detail/yageo/RC0402FR-07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
1,RC0402FR-0720K5L,YAGEO,R305,20k5,https://www.digikey.com/en/products/detail/yageo/RC0402FR-07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
1,RC0402FR-0731K6L,YAGEO,R306,31k6,https://www.digikey.com/en/products/detail/yageo/RC0402FR-07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
3,RC0402FR-07113KL,YAGEO,"R308,R806,R906",113k,https://www.digikey.com/en/products/detail/yageo/RC0402FR-07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
1,RC0402FR-0730K9L,YAGEO,R309,30k9,https://www.digikey.com/en/products/detail/yageo/RC0402FR-07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
3,RT0402BRD07105KL,YAGEO,"R310,R312,R314",105k,https://www.digikey.com/en/products/detail/yageo/RT0402BRD07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
3,ERA-2AEB203X,Panasonic,"R311,R313,R315",20k,https://www.digikey.com/en/products/detail/panasonic-industr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
10,RC0402FR-0733RL,YAGEO,"R405,R406,R407,R501,R502,R503,R504,R505,R506,R1002",33,https://www.digikey.com/en/products/detail/yageo/RC0402FR-07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
2,CRCW04024K70FKED,Vishay Dale,"R408,R409",4k7,https://www.digikey.com/en/products/detail/vishay-dale/CRCW0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
2,RC0402FR-07680RL,YAGEO,"R510,R511",680,https://www.digikey.com/en/products/detail/yageo/RC0402FR-07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
1,CRGP0603F10R,TE Connectivity,R604,10,https://www.digikey.com/en/products/detail/te-connectivity-p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
